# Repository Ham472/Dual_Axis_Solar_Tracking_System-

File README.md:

# Dual_Axis_Solar_Tracking_System-
A system that tracks sunlight direction using LDR sensors and automatically adjust the solar panel orientation. 

## Collaborators
1. Masika - Supervisor
2.

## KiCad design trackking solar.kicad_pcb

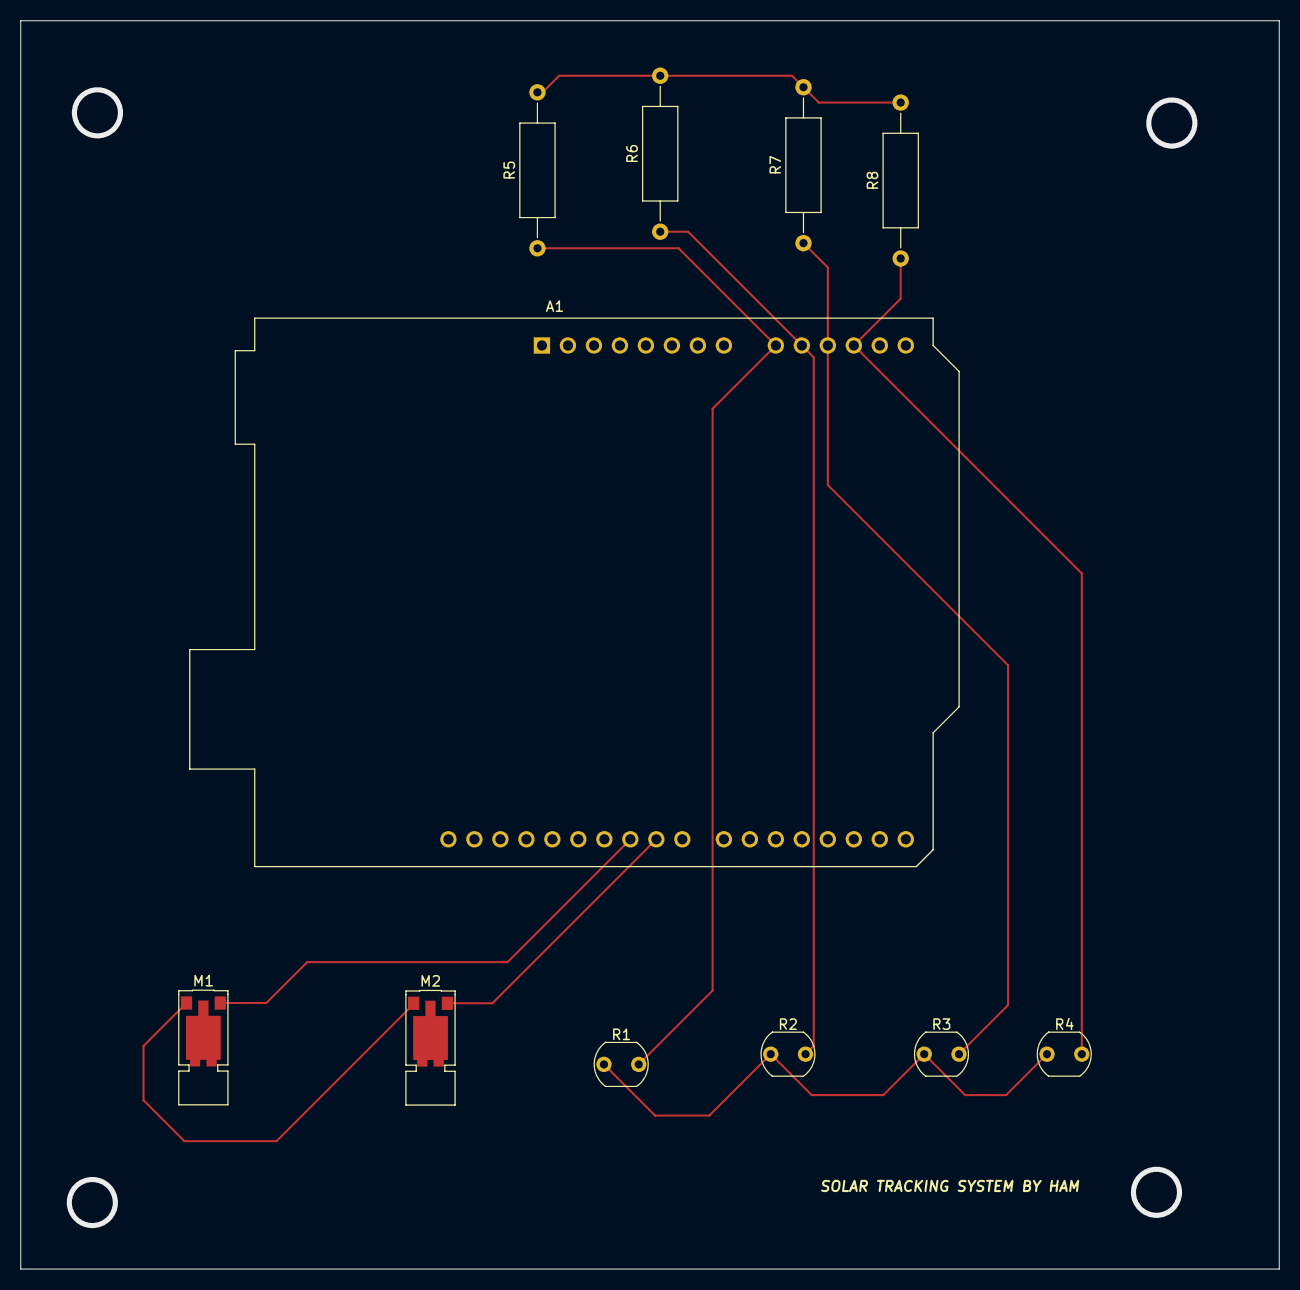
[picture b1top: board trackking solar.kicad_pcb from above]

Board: 2 copper layers, 123.0 x 122.0 mm, 11 parts (0 on the bottom side), 9 nets.

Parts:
A1: Arduino_UNO_R3
M1, M2: Motor_Servo; Vybronics_VZ30C1T8219732L
R1, R2, R3, R4: LDR07; R_LDR_5.1x4.3mm_P3.4mm_Vertical
R5, R6, R7, R8: R; R_Axial_DIN0309_L9.0mm_D3.2mm_P15.24mm_Horizontal

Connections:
unnamed: A1.9 (A0), R1.2, R5.1
unnamed: A1.10 (A1), R2.2, R6.1
unnamed: A1.11 (A2), R3.2, R7.1
unnamed: A1.12 (A3), R4.2, R8.1
unnamed: A1.24 (D9), M2.2 (+)
unnamed: A1.25 (D10), M1.2 (+)
unnamed: M1.1 (PWM), M2.1 (PWM)
unnamed: R1.1, R2.1, R3.1, R4.1
unnamed: R5.2, R6.2, R7.2, R8.2
